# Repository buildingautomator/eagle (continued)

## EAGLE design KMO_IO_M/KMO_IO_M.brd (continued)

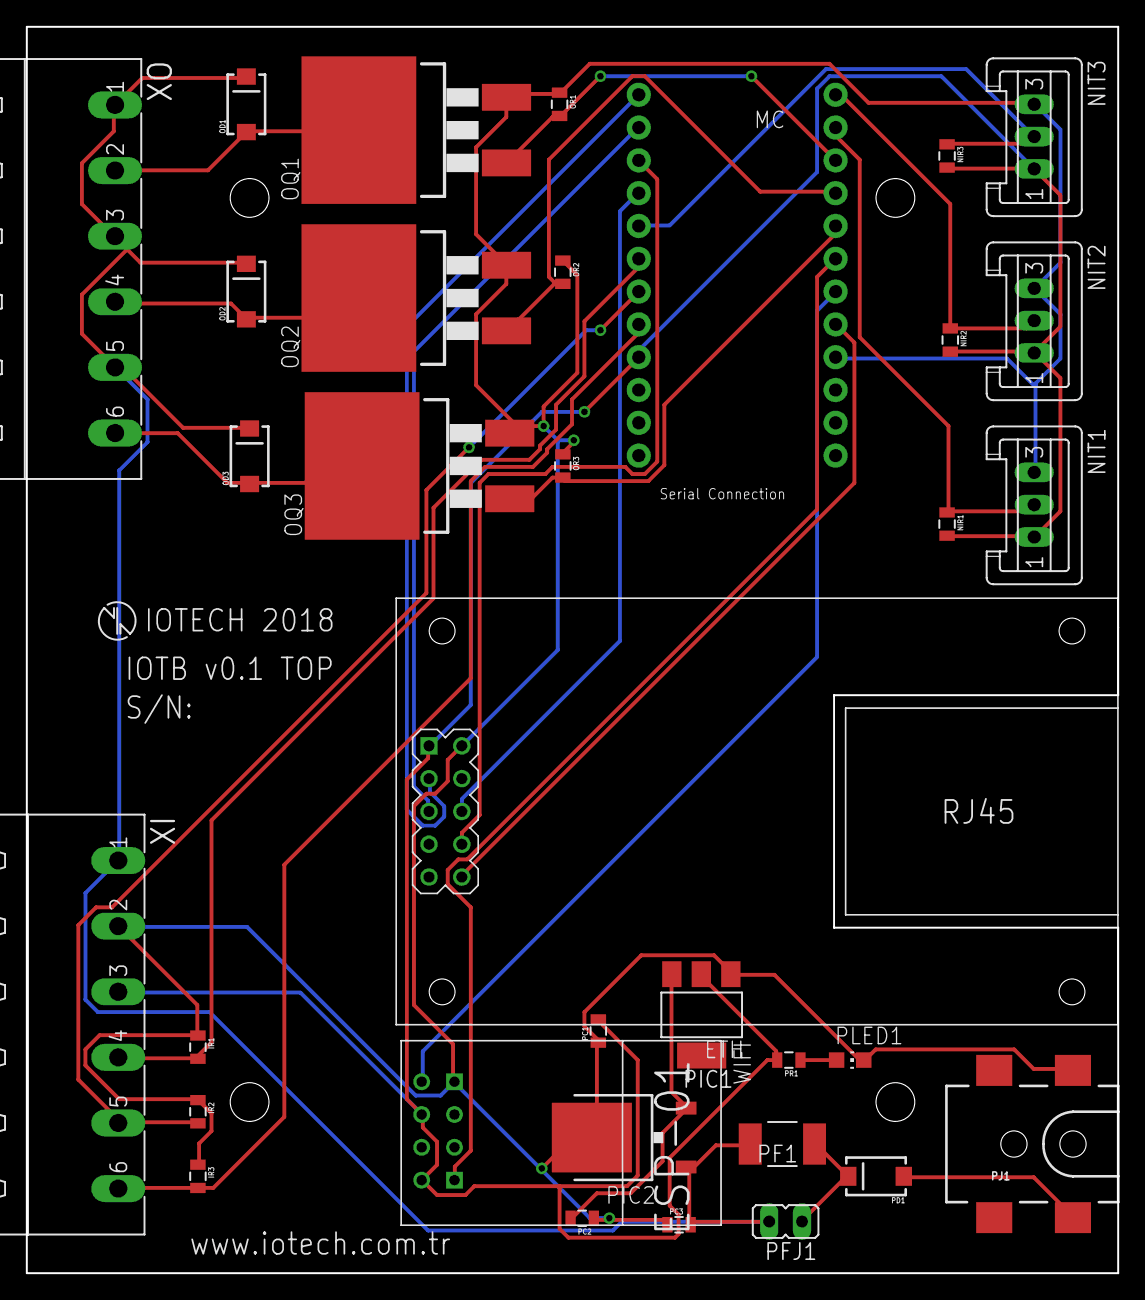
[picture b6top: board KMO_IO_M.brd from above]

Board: 2 copper layers, 84.5 x 96.5 mm, 34 parts (0 on the bottom side), 26 nets.
